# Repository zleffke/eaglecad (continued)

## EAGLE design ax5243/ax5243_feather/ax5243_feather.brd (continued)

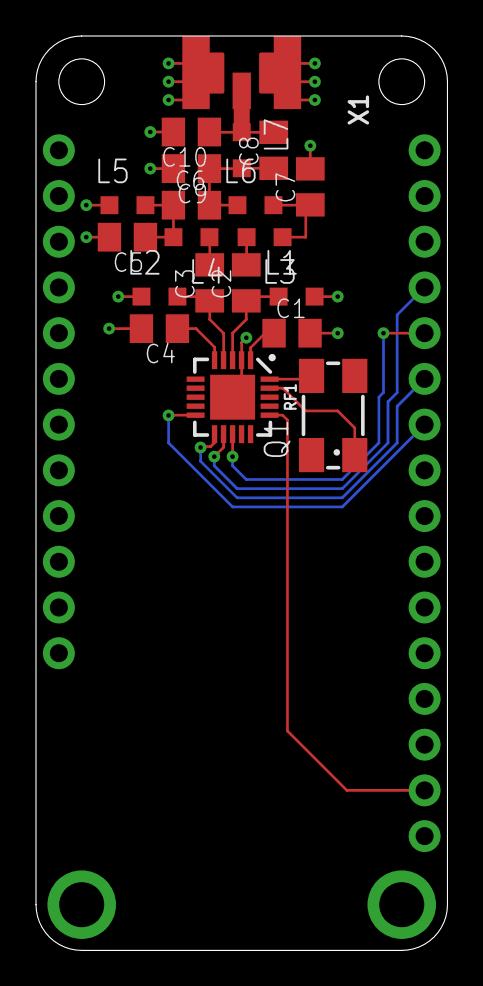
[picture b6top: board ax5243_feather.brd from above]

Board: 2 copper layers, 22.9 x 50.8 mm, 21 parts (0 on the bottom side), 19 nets.

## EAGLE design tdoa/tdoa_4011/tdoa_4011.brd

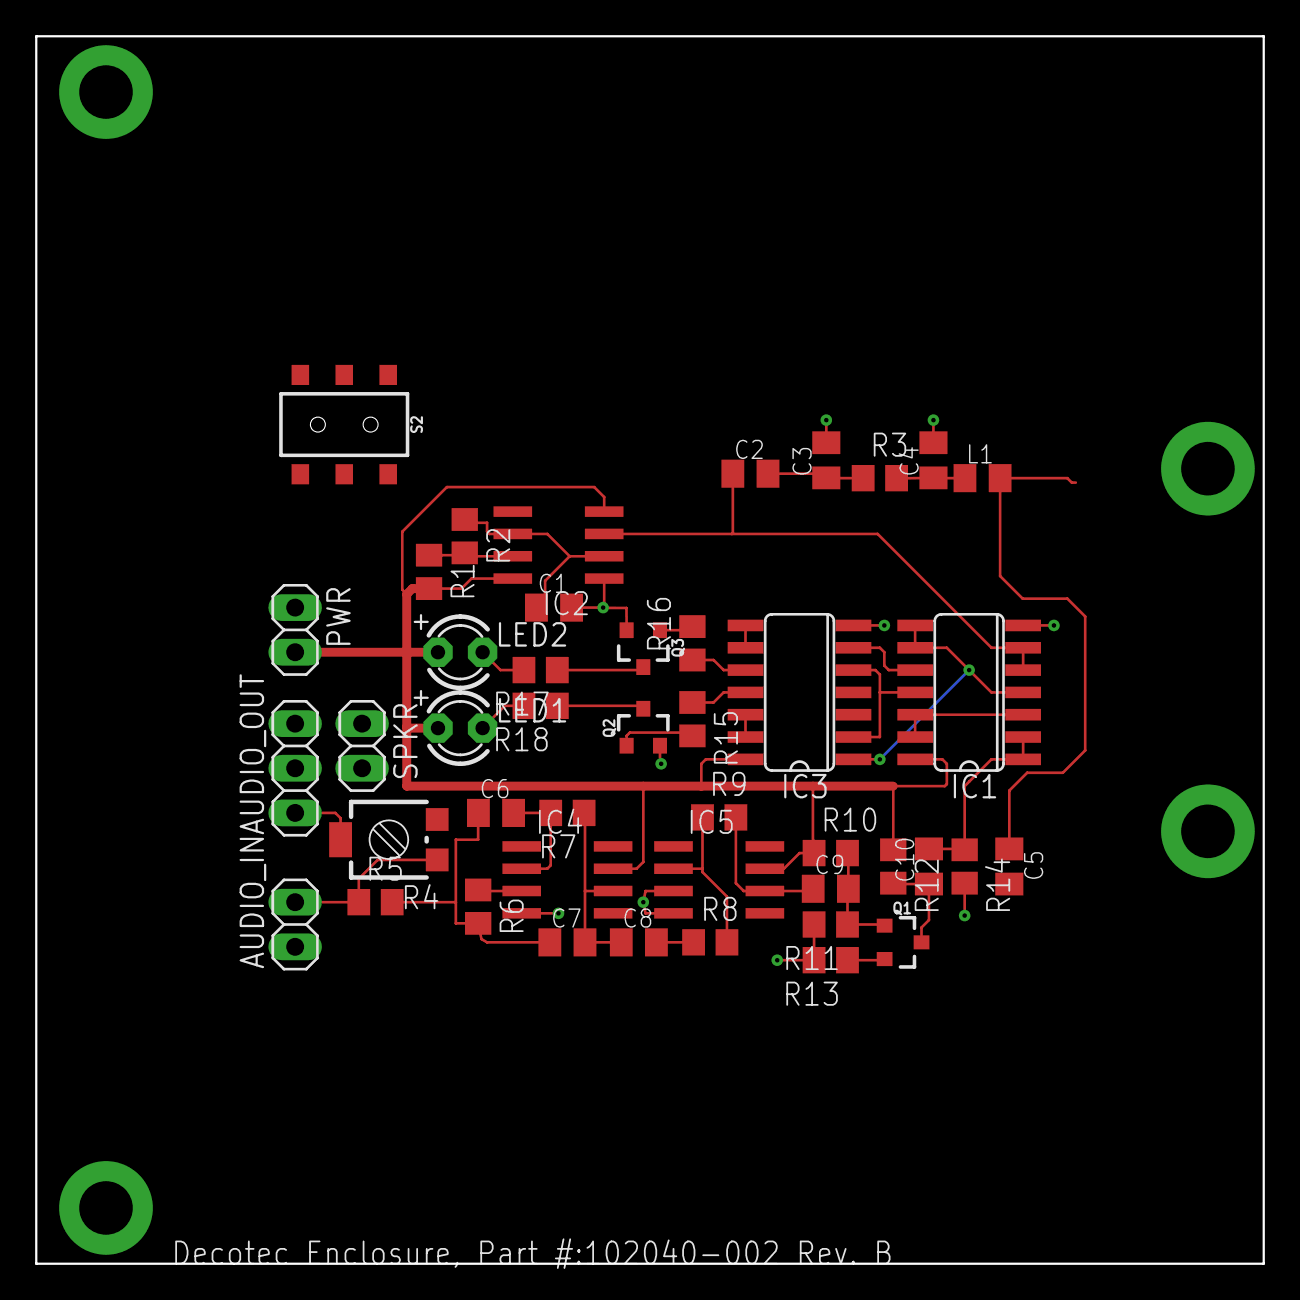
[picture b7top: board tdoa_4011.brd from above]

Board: 2 copper layers, 69.8 x 69.8 mm, 45 parts (0 on the bottom side), 38 nets.

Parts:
AUDIO_IN: 1X02
AUDIO_OUT: 1X03
C1: 0.0022uF; C0805K
C2, C3, C4, C5: C0805K
C6, C7: 0.01uF; C0805K
C8: 10uF; C0805K
C9: 0.001uF; C0805K
C10: 0.047uF; C0805K
IC1, IC3: 4011D; SO14
IC2: NE555D; SO08
IC4, IC5: LM741D; SO08
L1: L-US0805K; C0805K
LED1, LED2: LED3MM
PWR: 1X02
Q1, Q2, Q3: 600mA/40V; SOT23-3
R1, R3, R6, R8: 1k; R0805
R2, R7: 330k; R0805
R4: 500k; RTRIM3314G
R5: 33k; R0805
R9: 10k; R0805
R10: 82k; R0805
R11, R15, R16: 100k; R0805
R12: 8.2k; R0805
R13: 390; R0805
R14: 1M; R0805
R17, R18: 560; R0805
S2: SWITCH_DPDT_SMD_AYZ0202
SPKR: 1X02
U$1: DECOTEC_102040-002B

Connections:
GND: AUDIO_IN.1, AUDIO_OUT.3, C1.2, C3.2, C4.2, IC1.7, IC2.1, IC3.7, IC4.4, IC5.3, IC5.4, PWR.1, Q2.2, Q3.2, R11.2, R13.2, R14.2, SPKR.1, U$1.P$1, U$1.P$2, U$1.P$3, U$1.P$4
IN_FILT: C10.2, IC1.1, IC1.2, R14.1
IN_GEN: C2.1, IC1.5, IC1.6, IC2.3
unnamed: IC1.4, IC1.8, IC1.9, IC3.1
unnamed: IC2.7, R1.1, R2.2
unnamed: C1.1, IC2.2, IC2.6, R2.1
unnamed: C2.2, C3.1, R3.1
unnamed: C4.1, L1.1, R3.2
unnamed: AUDIO_OUT.1, R4.2
unnamed: C5.1, L1.2
unnamed: AUDIO_IN.2, R4.3, R5.1
unnamed: C6.1, C7.1, R5.2, R6.2
unnamed: IC4.3, R6.1
unnamed: C6.2, IC4.2, R7.2
unnamed: C7.2, C8.1, IC4.6, R7.1
unnamed: C8.2, R8.1
unnamed: IC5.2, R8.2, R9.1
unnamed: C9.1, IC5.6, R9.2
unnamed: C9.2, Q1.1, R10.2, R11.1
unnamed: Q1.2, R13.1
unnamed: C10.1, Q1.3, R12.2
unnamed: IC1.3, IC1.12, IC1.13
unnamed: IC1.11, IC3.2, IC3.5
unnamed: IC3.4, S2.1, S2.6
unnamed: IC1.10, IC3.6
unnamed: IC3.3, S2.3, S2.4
unnamed: IC3.12, IC3.13, S2.5
unnamed: IC3.8, IC3.9, S2.2
unnamed: Q2.3, R18.1
unnamed: LED1.K, R18.2
unnamed: Q3.3, R17.1
unnamed: LED2.K, R17.2
unnamed: IC3.11, R15.1
unnamed: Q2.1, R15.2
unnamed: IC3.10, R16.1
unnamed: Q3.1, R16.2
SPKR+: AUDIO_OUT.2, SPKR.2
VCC: IC1.14, IC2.4, IC2.8, IC3.14, IC4.7, IC5.7, LED1.A, LED2.A, PWR.2, R1.2, R10.1, R12.1

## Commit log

2017-07-01 KJ4QLP custom component library
2017-07-01 initial commit of AX5243 projects
2017-07-01 committing description document for Eagle CAD projects
2017-07-11 catching up commits, can't remember whats new in this one.
2017-07-11 adding feather layout for ax5043 RFIC.
2017-07-11 adding TDOA project
2017-07-11 adding gitignore file, currently ignores Eagle Files with '#' sign in file extension.
2017-07-12 removing files with # in extensions
2017-07-17 initial commit of RFM69 projects folder. First design includes radio, GPS, relay, SD Card. Based on Adafruit 'Feather' Stack up, but single board.
2017-07-17 not sure why the board wasn't part of the initial commit.
2017-07-17 updated pinout document, not done.
2017-07-18 fixing trash files for pinouts and board
2017-08-19 minor changes
2017-08-25 initial commit of RFM69 project that will include a better front end.
2017-08-29 updated kj4qlp library, RF PA modules and associated added
2017-08-29 New project, RFM69 with Mitsubishi MOSFET PA and PGA103 LNA and associated switching. incomplete, but mostly done.
2017-08-29 initial commit of tape measure dipole antenna boards.
2017-08-29 lots of detail updates, including test point additions, need to clean up silk screen.....
2017-09-08 new components added to library
2017-09-08 Final version of Rev- board including Gerbers and Osh Park pictures. This is the version sent to Osh PArk for fab.
2017-09-08 minor updates
2017-09-08 initial commit of a different variant of RFM69 board with PA, beginnings of version with more telemetry.
2017-09-19 board outline based on decotec part updated due to change to library. ALignment of SMA and SD Card are incorrect due to the improperly spaced BNC cutouts. Library is now fixed......Starting Rev-A boa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
2017-09-19 copy and paste of rev-. Fixed alignment of SMA connector and SD Card to reflect updated board outline and decotec enclosure.
2017-09-21 Changed PTT pin from physical pin 22 to physical pin 25 which is mapped to arduino digital pin 4. This was done because there is no mapping of physical pin 22 to an arduino digital pin for the feathe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
2017-10-06 Final updates. Final Gerbers submitted for fabrication.
2017-10-12 PGA-103+ Low Noise Amplifier with 433.92 MHz, 5MHz wide, SAW BPF. This commit is the version sent to Osh Park for Fab.
2018-09-01 adding readme....moving projects to their own repos.
2021-02-22 mass commit
